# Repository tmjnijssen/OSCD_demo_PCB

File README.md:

# OSCD Demo PCB

A demonstration / teaching PCB built by the [Open Science Community Delft](https://www.tudelft.nl/en/library/open-science-community-delft) to show what an open hardware project looks like in practice: full sources, an open licence, and everything needed to have the board made and reprogrammed by anyone.

It is a round, ~93 mm ESP32-C3 board shaped like the OSCD logo, with a ring of 12 addressable RGB LEDs, three sensors on a shared I²C bus, capacitive touch pads, and three push buttons. Plug it into USB-C, and the demo firmware lights the ring in response to tilt, touch, ambient light, and button presses.

| | |
|---|---|
| **Revision** | 1.0 |
| **Designer** | Dr. ir. Tim M. J. Nijssen, Open Science Community Delft |
| **Licence** | [CERN-OHL-P v2](LICENSE) (permissive) |
| **EDA tool** | KiCad (2026-era release — see [Opening the design](#opening-the-design)) |

---

## Features

| Block | Part | Interface |
|---|---|---|
| Microcontroller | ESP32-C3-MINI-1 (RISC-V, Wi-Fi + BLE, native USB) | — |
| RGB LEDs | 12 × WS2812B-2020, in a 63 mm ring | 1-wire, `GPIO8` |
| IMU | LSM6DS3 — 3-axis accelerometer + gyroscope | I²C `0x6A` |
| Ambient light | APDS-9306-065 | I²C `0x52` |
| Capacitive touch | MPR121 — 12 electrodes (6 buttons + 6-pad slider) | I²C `0x5A`, IRQ on `GPIO10` |
| Buttons | 3 × user push button, plus RESET and BOOT | `GPIO0/1/2` |
| Power | USB-C 5 V → HT7533-1 LDO → 3.3 V | — |
| Breakout | 2 × 2×5 pin header (5 V, 3.3 V, GND, 9 GPIO) | 2.54 mm |
| Test points | 5 V, 3.3 V, SDA, SCL (each via 100 Ω) | — |

There is no USB-UART bridge — the ESP32-C3's native USB peripheral is wired straight to the USB-C connector, protected by a USBLC6-2SC6 ESD array.

## Quick start

1. **Power it.** Connect a USB-C cable to `J1`. The board is bus-powered; no battery or jumper setting is needed.
2. **Install the toolchain.** Arduino IDE with the *esp32* board package by Espressif, board **ESP32C3 Dev Module**, and **Tools → USB CDC On Boot: Enabled**.
3. **Flash the demo.** Open [`firmware_examples/test_sensors/test_sensors.ino`](firmware_examples/test_sensors/test_sensors.ino) and upload it. Because there is no auto-reset circuit you must enter the bootloader by hand: **hold BOOT (SW2), tap RESET (SW1), release BOOT**, then click Upload. Tap RESET again when the upload finishes.
4. **Watch it.** The ring plays a rainbow sweep at boot, then reacts to tilt, touch, and the three buttons. Open the Serial Monitor at 115200 baud for sensor readings.

Full setup notes, required libraries, and troubleshooting are in [`firmware_examples/README.md`](firmware_examples/README.md).

## Pinout

| ESP32-C3 pin | Function on this board | Also on |
|---|---|---|
| `GPIO0` | Button **SW4** (active low, RC-debounced) | `J2.6` |
| `GPIO1` | Button **SW3** (active low, RC-debounced) | `J2.7` |
| `GPIO2` | Button **SW5** (active low, RC-debounced) | `J2.3` |
| `GPIO3` | APDS-9306 interrupt | `J2.4` |
| `GPIO4` | LSM6DS3 `INT1` | `J2.9` |
| `GPIO5` | LSM6DS3 `INT2` | `J3.3` |
| `GPIO6` | **I²C SCL** (4.7 kΩ pull-up) | `J3.4`, `TP5` |
| `GPIO7` | **I²C SDA** (4.7 kΩ pull-up) | `J3.5`, `TP6` |
| `GPIO8` | WS2812B data out → `D1` | `J3.6` |
| `GPIO9` | BOOT button **SW2** (strapping pin) | `J3.7` |
| `GPIO10` | MPR121 `IRQ` | `J2.8` |
| `GPIO18/19` | USB D− / D+ | — |
| `GPIO20/21` | UART0 RX / TX | `J3.8`, `J3.9` |
| `EN` | RESET button **SW1** | `J2.5` |

**Header pinouts** (2×5, 2.54 mm, odd/even numbering):

```
J2:  1 +5V    2 +3V3    3 GPIO2   4 GPIO3   5 EN
     6 GPIO0  7 GPIO1   8 GPIO10  9 GPIO4  10 GND

J3:  1 +5V    2 +3V3    3 GPIO5   4 GPIO6   5 GPIO7
     6 GPIO8  7 GPIO9   8 GPIO20  9 GPIO21 10 GND
```

**LED ring order:** `D1` sits at the 9 o'clock position and the chain `D1 → D2 → … → D12` runs clockwise, 30° apart.

**Touch electrodes:** `TP2` is the inner 6-pad slider on `ELE0…ELE5`; `TP1` is the outer ring of 6 buttons on `ELE6…ELE11`.

## Repository layout

```
OSCD_demo_PCB.kicad_pro     KiCad project
OSCD_demo_PCB.kicad_sch     Schematic (single sheet)
OSCD_demo_PCB.kicad_pcb     Board layout (4 layers)
schematic.pdf               Rendered schematic, for reading without KiCad
assets/
  OSCD_demo_PCB_symbols.kicad_sym    Project-local symbols
  OSCD_demo_PCB_footprints.pretty/   Project-local footprints (ESP32 module,
                                     touch pads, WS2812B-2020, logo, switches)
  graphics/                          OSCD logo artwork (DXF)
bom/ibom.html               Interactive HTML BOM for hand assembly
production/                 Fabrication outputs (gerbers, drill, BOM, CPL)
firmware_examples/          Arduino sketches
docs/                       Hardware and manufacturing documentation
```

## Opening the design

The sources were saved by a 2026-era KiCad release (schematic file format `20260306`, board format `20260206`). Open them with that release or newer; older KiCad versions will refuse the files.

Symbol and footprint libraries are project-local and resolved through `${KIPRJMOD}` in `sym-lib-table` / `fp-lib-table`, so cloning the repository and opening `OSCD_demo_PCB.kicad_pro` is enough — nothing has to be installed into your global libraries.

## Documentation

- **[docs/hardware.md](docs/hardware.md)** — how each subsystem works, jumper/configuration options, and design notes.
- **[docs/manufacturing.md](docs/manufacturing.md)** — board specification, ordering, and how to regenerate the fabrication files.
- **[firmware_examples/README.md](firmware_examples/README.md)** — toolchain setup, upload procedure, and what the demo does.

## Licence

Hardware and firmware are released under the **CERN Open Hardware Licence Version 2 – Permissive** ([`LICENSE`](LICENSE)). You may use, study, modify, manufacture and sell boards based on this design, including in closed-source products, provided you keep the copyright and licence notices and do not imply endorsement.

The OSCD logo and name are project branding; please replace them with your own if you distribute modified boards.

## Credits

Designed by Dr. ir. Tim M. J. Nijssen for the Open Science Community Delft.

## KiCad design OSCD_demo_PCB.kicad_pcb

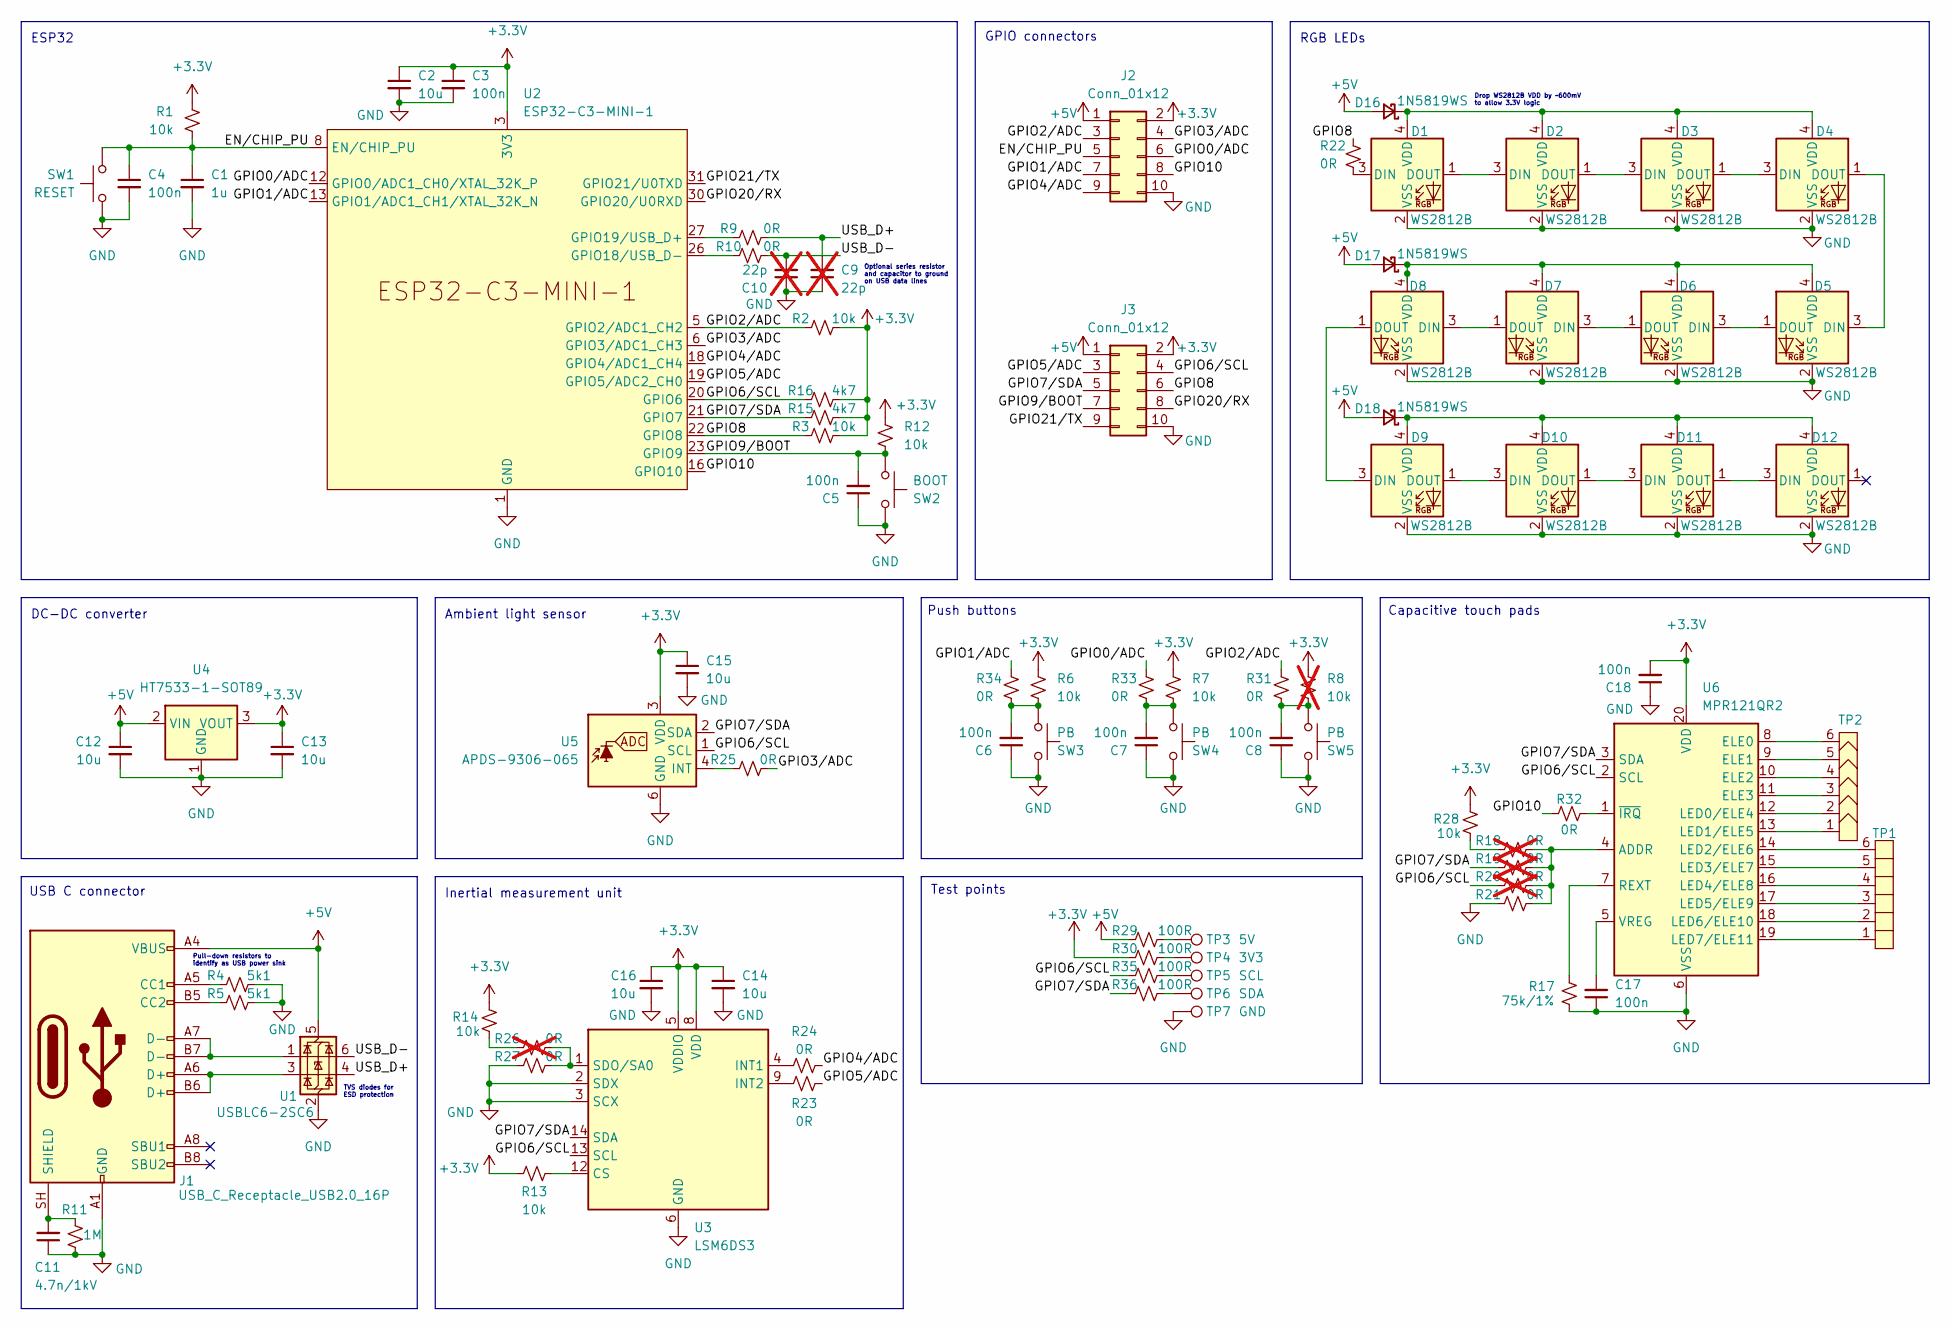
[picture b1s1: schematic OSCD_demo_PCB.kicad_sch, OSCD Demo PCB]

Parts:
C1: 1u; C_0805_2012Metric_Pad1.18x1.45mm_HandSolder; LCSC C28323
C2, C12, C13, C14, C15, C16: 10u; C_0805_2012Metric_Pad1.18x1.45mm_HandSolder; LCSC C15850
C3, C4, C5, C6, C7, C8, C17, C18: 100n; C_0805_2012Metric_Pad1.18x1.45mm_HandSolder; LCSC C49678
C9, C10: 22p; C_0805_2012Metric_Pad1.18x1.45mm_HandSolder; not fitted
C11: 4.7n/1kV; C_0805_2012Metric_Pad1.18x1.45mm_HandSolder; LCSC C565695
D1, D2, D3, D4, D5, D6, D7, D8, D9, D10, D11, D12: WS2812B; LED_WS2812B-2020_PLCC4_2.0x2.0mm; LCSC C2976072
D16, D17, D18: 1N5819WS; D_SOD-323; LCSC C191023
J1: USB_C_Receptacle_USB2.0_16P; USB_C_Receptacle_GCT_USB4105-xx-A_16P_TopMnt_Horizontal; LCSC C393939
J2, J3: Conn_01x12; PinHeader_2x05_P2.54mm_Vertical
R1, R2, R3, R6, R7, R12, R13, R14, R28: 10k; R_0805_2012Metric_Pad1.20x1.40mm_HandSolder; LCSC C17414
R4, R5: 5k1; R_0805_2012Metric_Pad1.20x1.40mm_HandSolder; LCSC C27834
R8: 10k; R_0805_2012Metric_Pad1.20x1.40mm_HandSolder; not fitted
R9, R10, R21, R22, R23, R24, R25, R27, R31, R32, R33, R34: 0R; R_0805_2012Metric_Pad1.20x1.40mm_HandSolder; LCSC C17477
R11: 1M; R_0805_2012Metric_Pad1.20x1.40mm_HandSolder; LCSC C17514
R15, R16: 4k7; R_0805_2012Metric_Pad1.20x1.40mm_HandSolder; LCSC C17673
R17: 75k/1%; R_0805_2012Metric_Pad1.20x1.40mm_HandSolder; LCSC C17819
R18, R19, R20, R26: 0R; R_0805_2012Metric_Pad1.20x1.40mm_HandSolder; not fitted
R29, R30, R35, R36: 100R; R_0805_2012Metric_Pad1.20x1.40mm_HandSolder; LCSC C17408
SW1: RESET; SMD_SW_1P1T_TS-1088-AR02016; LCSC C720477
SW2: BOOT; SMD_SW_1P1T_TS-1088-AR02016; LCSC C720477
SW3, SW4, SW5: PB; SW_SPST_PTS645Sx43SMTR92; LCSC C2837531
TP1: 6_pad_touch_slider; 6_pad_touch_buttons
TP2: 6_pad_touch_slider
TP3: 5V; TestPoint_Pad_D2.0mm
TP4: 3V3; TestPoint_Pad_D2.0mm
TP5: SCL; TestPoint_Pad_D2.0mm
TP6: SDA; TestPoint_Pad_D2.0mm
TP7: GND; TestPoint_Pad_D2.0mm
U1: USBLC6-2SC6; SOT-23-6; LCSC C7519
U2: ESP32-C3-MINI-1; LCSC C2838502
U3: LSM6DS3; LGA-14_3x2.5mm_P0.5mm_LayoutBorder3x4y; LCSC C967633
U4: HT7533-1-SOT89; SOT-89-3; LCSC C14289
U5: APDS-9306-065; Broadcom_DFN-6_2x2mm_P0.65mm; LCSC C2649498
U6: MPR121QR2; UQFN-20_3x3mm_P0.4mm; LCSC C91322

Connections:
+3.3V: C2.1, C3.1, C13.1, C14.1, C15.1, C16.1, C18.2, J2.2, J3.2, R1.1, R2.2, R3.2, R6.2, R7.2, R8.2, R12.1, R13.1, R14.2, R15.2, R16.2, R28.2, R30.1, U2.3 (3V3), U3.5 (VDDIO), U3.8 (VDD), U4.3 (VOUT), U5.3 (VDD), U6.20 (VDD)
+5V: C12.1, D16.2 (A), D17.2 (A), D18.2 (A), J1.A4 (VBUS), J1.A9 (VBUS), J1.B4 (VBUS), J1.B9 (VBUS), J2.1, J3.1, R29.1, U1.5 (VBUS), U4.2 (VIN)
/EN/CHIP_PU: C1.1, C4.1, J2.5, R1.2, SW1.2, U2.8 (EN/CHIP_PU)
/GPIO0/ADC: J2.6, R33.1, U2.12 (GPIO0/ADC1_CH0/XTAL_32K_P)
/GPIO1/ADC: J2.7, R34.1, U2.13 (GPIO1/ADC1_CH1/XTAL_32K_N)
/GPIO2/ADC: J2.3, R2.1, R31.1, U2.5 (GPIO2/ADC1_CH2)
/GPIO3/ADC: J2.4, R25.1, U2.6 (GPIO3/ADC1_CH3)
/GPIO4/ADC: J2.9, R24.1, U2.18 (GPIO4/ADC1_CH4)
/GPIO5/ADC: J3.3, R23.1, U2.19 (GPIO5/ADC2_CH0)
/GPIO6/SCL: J3.4, R16.1, R20.2, R35.1, U2.20 (GPIO6), U3.13 (SCL), U5.1 (SCL), U6.2 (SCL)
/GPIO7/SDA: J3.5, R15.1, R19.2, R36.1, U2.21 (GPIO7), U3.14 (SDA), U5.2 (SDA), U6.3 (SDA)
/GPIO8: J3.6, R3.1, R22.1, U2.22 (GPIO8)
/GPIO9/BOOT: C5.2, J3.7, R12.2, SW2.1, U2.23 (GPIO9)
/GPIO10: J2.8, R32.2, U2.16 (GPIO10)
/GPIO20/RX: J3.8, U2.30 (GPIO20/U0RXD)
/GPIO21/TX: J3.9, U2.31 (GPIO21/U0TXD)
/USB_D+: C9.2, R9.2, U1.4 (I/O2)
/USB_D-: C10.2, R10.2, U1.6 (I/O1)
GND: C1.2, C2.2, C3.2, C4.2, C5.1, C6.1, C7.1, C8.1, C9.1, C10.1, C11.1, C12.2, C13.2, C14.2, C15.2, C16.2, C17.1, C18.1, D1.2 (VSS), D2.2 (VSS), D3.2 (VSS), D4.2 (VSS), D5.2 (VSS), D6.2 (VSS), D7.2 (VSS), D8.2 (VSS), D9.2 (VSS), D10.2 (VSS), D11.2 (VSS), D12.2 (VSS), J1.A1 (GND), J1.A12 (GND), J1.B1 (GND), J1.B12 (GND), J2.10, J3.10, R4.2, R5.2, R11.1, R17.1, R21.2, R27.2, SW1.1, SW2.2, SW3.2, SW4.2, SW5.2, TP7.1 (1_1), U1.2 (GND), U2.1 (GND), U2.2 (GND), U2.11 (GND), U2.14 (GND), U2.36 (GND), U2.37 (GND), U2.38 (GND), U2.39 (GND), U2.40 (GND), U2.41 (GND), U2.42 (GND), U2.43 (GND), U2.44 (GND), U2.45 (GND), U2.46 (GND), U2.47 (GND), U2.48 (GND), U2.49 (GND), U2.50 (GND), U2.51 (GND), U2.52 (GND), U2.53 (GND), U3.2 (SDX), U3.3 (SCX), U3.6 (GND), U3.7 (GND), U4.1 (GND), U5.6 (GND), U6.6 (VSS)
unnamed: C6.2, R6.1, R34.2, SW3.1
unnamed: C7.2, R7.1, R33.2, SW4.1
unnamed: C8.2, R8.1, R31.2, SW5.1
unnamed: D1.3 (DIN), R22.2
unnamed: D1.1 (DOUT), D2.3 (DIN)
unnamed: D1.4 (VDD), D2.4 (VDD), D3.4 (VDD), D4.4 (VDD), D16.1 (K)
unnamed: D2.1 (DOUT), D3.3 (DIN)
unnamed: D3.1 (DOUT), D4.3 (DIN)
unnamed: D4.1 (DOUT), D5.3 (DIN)
unnamed: D5.1 (DOUT), D6.3 (DIN)
unnamed: D6.1 (DOUT), D7.3 (DIN)
unnamed: D7.1 (DOUT), D8.3 (DIN)
unnamed: D8.1 (DOUT), D9.3 (DIN)
unnamed: D9.1 (DOUT), D10.3 (DIN)
unnamed: D10.1 (DOUT), D11.3 (DIN)
unnamed: D9.4 (VDD), D10.4 (VDD), D11.4 (VDD), D12.4 (VDD), D18.1 (K)
unnamed: D11.1 (DOUT), D12.3 (DIN)
unnamed: D5.4 (VDD), D6.4 (VDD), D7.4 (VDD), D8.4 (VDD), D17.1 (K)
unnamed: J1.A5 (CC1), R4.1
unnamed: J1.B5 (CC2), R5.1
unnamed: J1.A6 (D+), J1.B6 (D+), U1.3 (I/O2)
unnamed: J1.A7 (D-), J1.B7 (D-), U1.1 (I/O1)
unnamed: C11.2, J1.SH (SHIELD), R11.2
unnamed: R14.1, R26.2
unnamed: R18.2, R28.1
unnamed: R29.2, TP3.1 (1_1)
unnamed: R30.2, TP4.1 (1_1)
unnamed: R35.2, TP5.1 (1_1)
unnamed: R36.2, TP6.1 (1_1)
unnamed: R10.1, U2.26 (GPIO18/USB_D-)
unnamed: R9.1, U2.27 (GPIO19/USB_D+)
unnamed: R13.2, U3.12 (CS)
unnamed: R24.2, U3.4 (INT1)
unnamed: R23.2, U3.9 (INT2)
unnamed: R26.1, R27.1, U3.1 (SDO/SA0)
unnamed: R25.2, U5.4 (INT)
unnamed: R18.1, R19.1, R20.1, R21.1, U6.4 (ADDR)
unnamed: TP2.6 (Pad_6), U6.8 (ELE0)
unnamed: TP2.5 (Pad_5), U6.9 (ELE1)
unnamed: TP2.4 (Pad_4), U6.10 (ELE2)
unnamed: TP2.3 (Pad_3), U6.11 (ELE3)
unnamed: TP2.2 (Pad_2), U6.12 (LED0/ELE4)
unnamed: TP2.1 (Pad_1), U6.13 (LED1/ELE5)
unnamed: TP1.6 (Pad_6), U6.14 (LED2/ELE6)
unnamed: TP1.5 (Pad_5), U6.15 (LED3/ELE7)
unnamed: TP1.4 (Pad_4), U6.16 (LED4/ELE8)
unnamed: TP1.3 (Pad_3), U6.17 (LED5/ELE9)
unnamed: TP1.2 (Pad_2), U6.18 (LED6/ELE10)
unnamed: TP1.1 (Pad_1), U6.19 (LED7/ELE11)
unnamed: R17.2, U6.7 (REXT)
unnamed: C17.2, U6.5 (VREG)
unnamed: R32.1, U6.1 (~IRQ)

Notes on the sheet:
DC-DC converter
Ambient light sensor
Push buttons
Optional series resistor and capacitor to ground on USB data lines
Inertial measurement unit
GPIO connectors
USB C connector
RGB LEDs
Test points
TVS diodes for ESD protection
ESP32
Drop WS2812B VDD by ~600mV to allow 3.3V logic
Capacitive touch pads
Pull-down resistors to identify as USB power sink

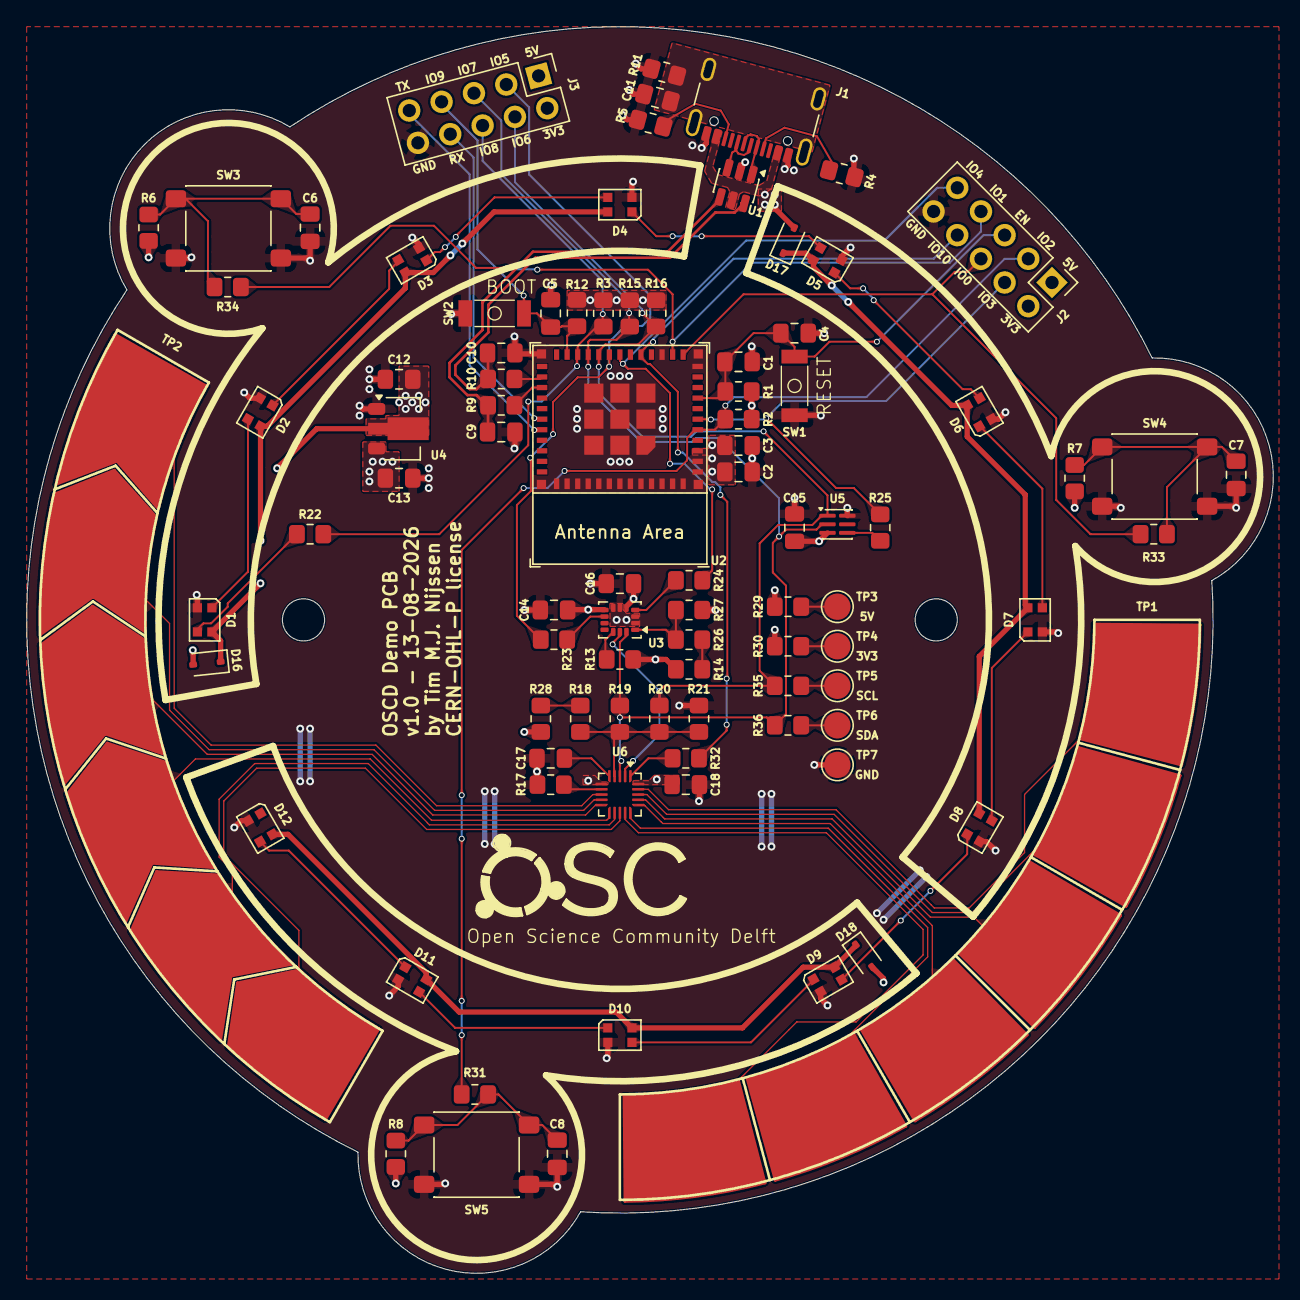
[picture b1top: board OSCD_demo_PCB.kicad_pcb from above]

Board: 4 copper layers, 94.6 x 94.6 mm, 90 parts (0 on the bottom side), 71 nets.

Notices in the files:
OSCD_demo_PCB.kicad_pcb:
CERN-OHL-P license
